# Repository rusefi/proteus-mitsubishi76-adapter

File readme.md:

https://github.com/rusefi/rusefi and https://github.com/mck1117/proteus

76 pin

2 gen DSM
1995-1999 Mitsubishi Eclipse and Eagle Talon Turbo DSM ECU Pinouts 

v6

Lancer up to 2005?

Our document, need work
[Connector Pinout Spreadsheet, with links to wiring drawings](https://docs.google.com/spreadsheets/d/1ZlcC5cdCwjYoV-z49MNaa9zpLiu_ZYBIx5H-j0F6QpI)

Norman notes https://docs.google.com/spreadsheets/d/1ddxDElQDG0ZjSaX5fpkFeflPWwk7OCHC93gru9Ey_9U

Random sources of info

https://my.prostreetonline.com/2013/09/05/faq-1g-and-2g-dsm-ecu-pinouts/

http://www.stealth316.com/2-ecu-terminals.htm

Compatible case:

MD329098

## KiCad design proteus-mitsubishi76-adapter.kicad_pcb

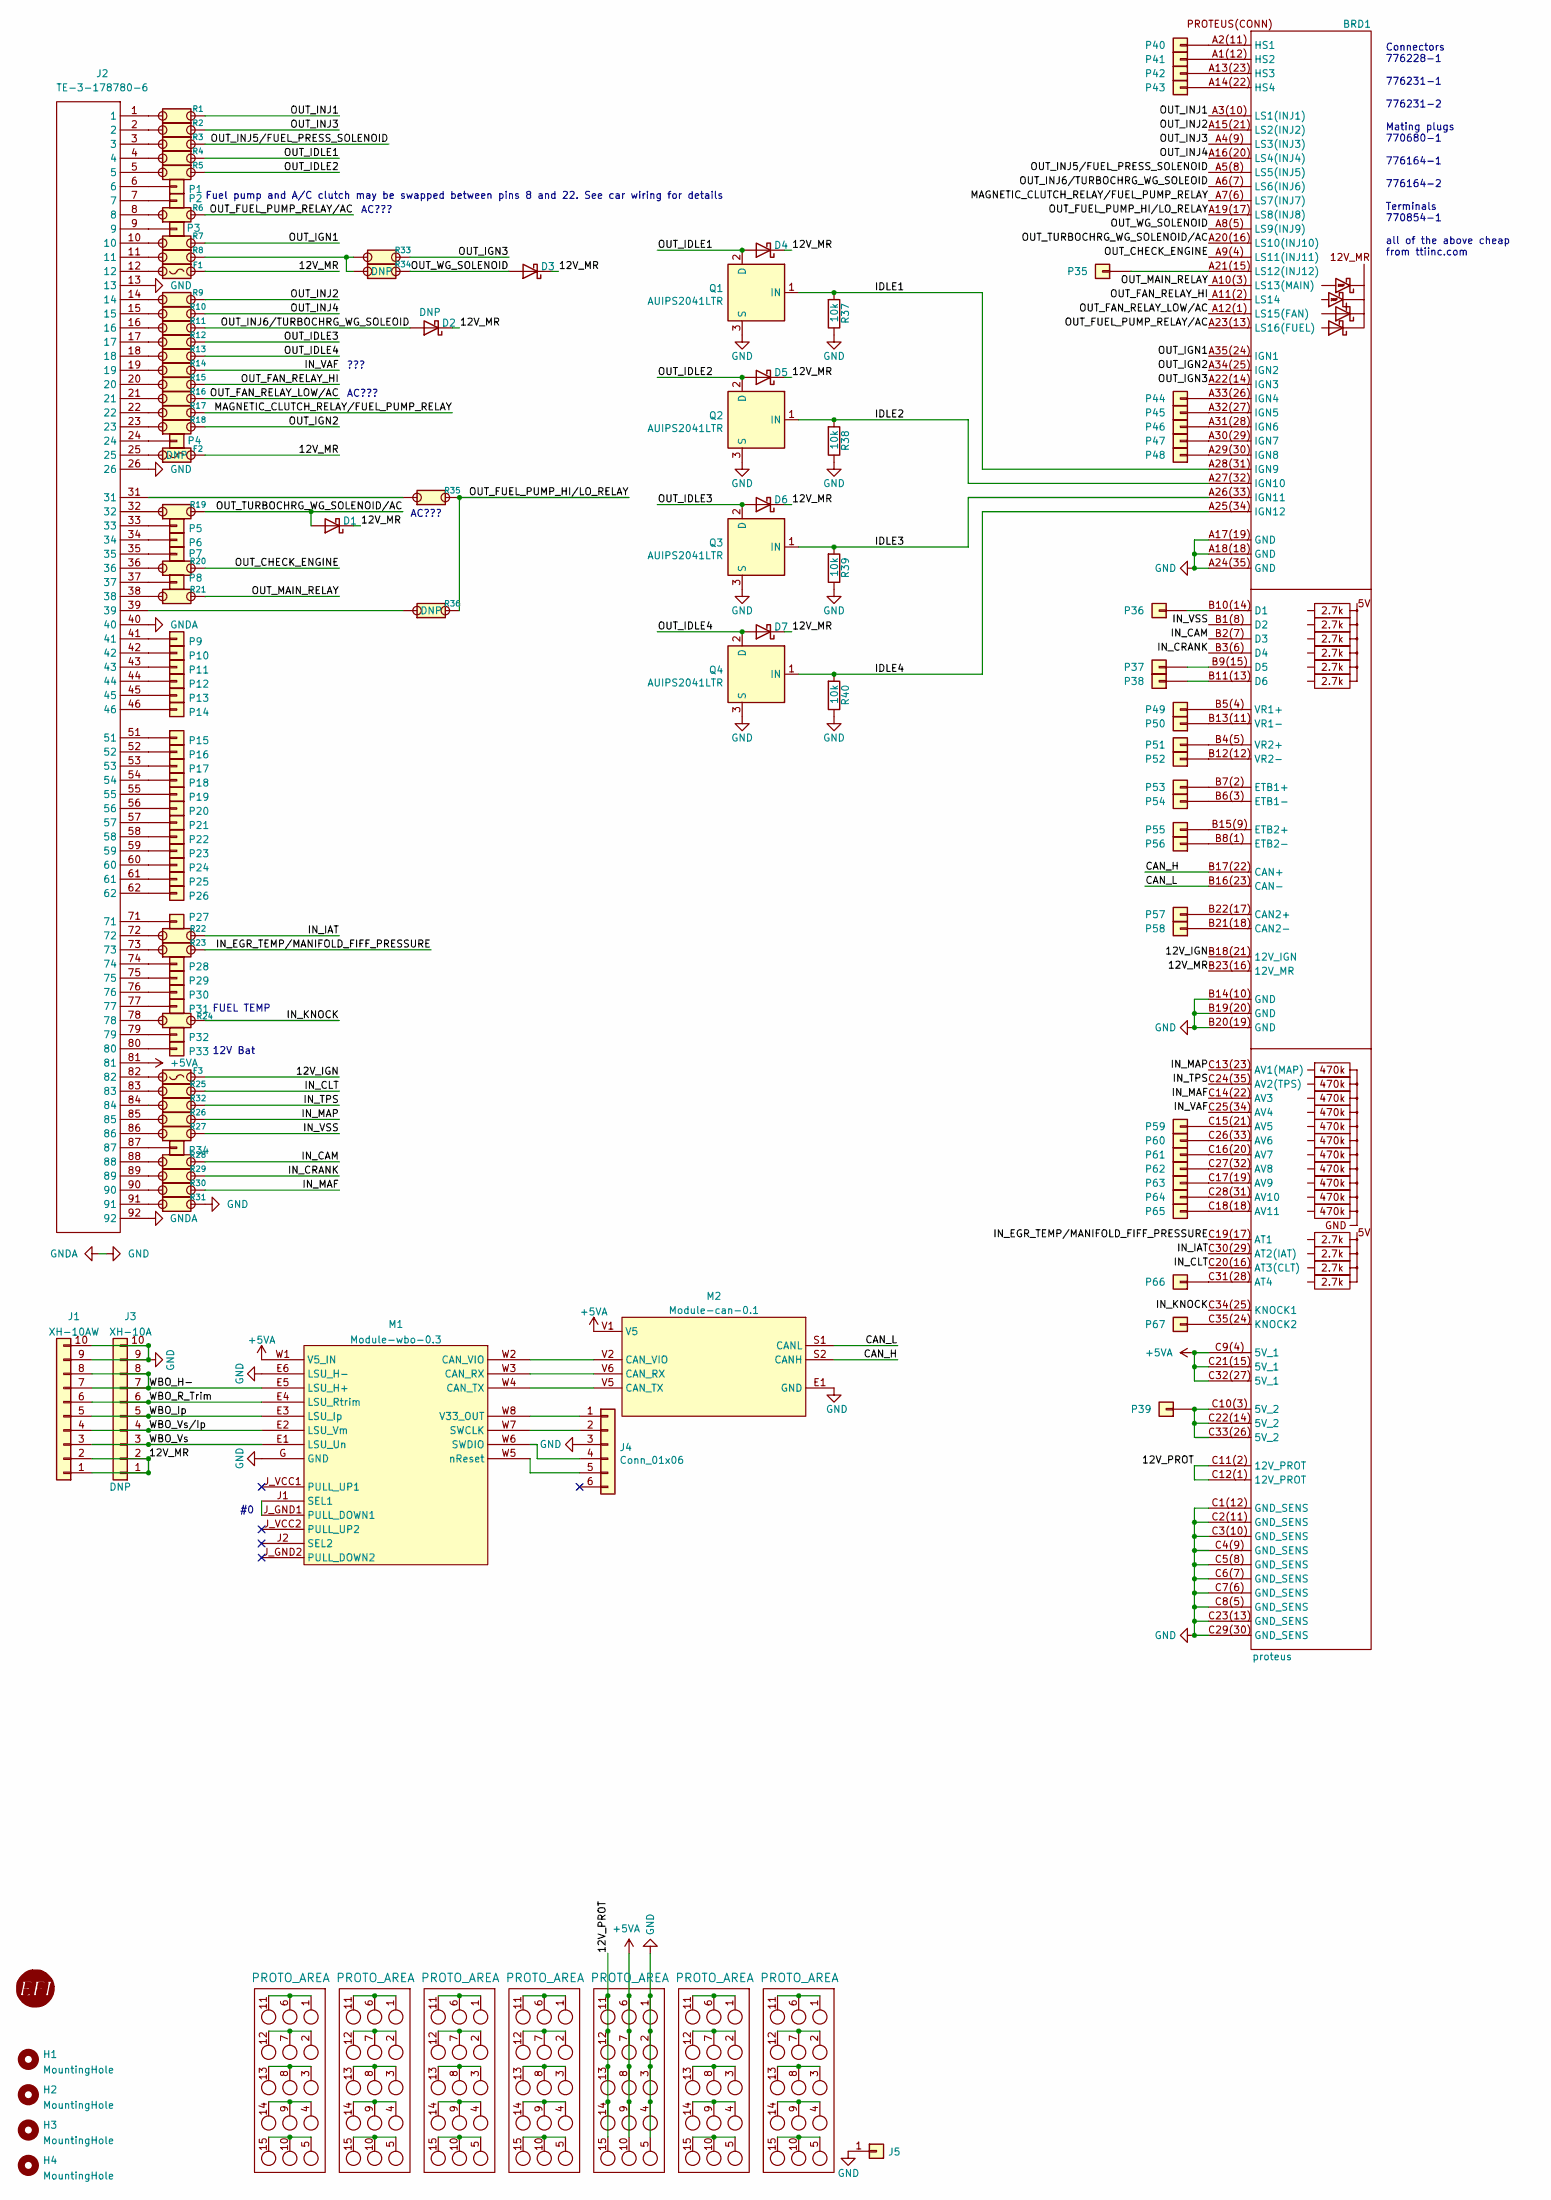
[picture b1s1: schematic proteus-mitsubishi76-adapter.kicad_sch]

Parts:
BRD1: proteus
D1, D3, D4, D5, D6, D7: D_Schottky; D_SMA; LCSC C8678
D2: DNP; D_SMA; LCSC_ext 0
F1, F3: Fuse-Pad-Pad; PAD-1206-PAD; LCSC C182446
F2: Fuse-Pad-Pad; PAD-1206-PAD
G1: RUSEFI_LOGO; rusefi_logo
G2, G3, G4, G5, G6, G7, G8: PROTO_AREA
H1, H2, H3, H4: MountingHole; MountingHole_5mm_Pad_TopOnly
J1: XH-10AW; JST_XH_S10B-XH-A_1x10_P2.50mm_Horizontal; LCSC C14652
J2: TE-3-178780-6
J3: XH-10A; JST_XH_B10B-XH-A_1x10_P2.50mm_Vertical; LCSC C8885
J4: Conn_01x06; PinHeader_1x06_P2.54mm_Vertical
J5: Conn_01x01; TestPoint_Pad_D4.0mm
M1: Module-wbo-0.3; wbo
M2: Module-can-0.1; can
P1, P2, P3, P4, P5, P6, P7, P8, P9, P10, P11, P12, P13, P14, P15, P16, P17, P18, P19, P20, P21, P22, P23, P24, P25, P26, P27, P28, P29, P30, P31, P32, P33, P34, P35, P36, P37, P38, P39, P40, P41, P42, P43, P44, P45, P46, P47, P48, P49, P50, P51, P52, P53, P54, P55, P56, P57, P58, P59, P60, P61, P62, P63, P64, P65, P66, P67: Pad; PAD-TH
Q1, Q2, Q3, Q4: AUIPS2041LTR; SOT-223; LCSC C113610
R1, R2, R3, R4, R5, R6, R7, R8, R9, R10, R11, R12, R13, R14, R15, R16, R17, R18, R19, R20, R21, R22, R23, R24, R25, R26, R27, R28, R29, R30, R31, R32, R33, R35: Jumper-Pad-Pad; PAD-0805-PAD; LCSC C17477
R34, R36: Jumper-Pad-Pad; PAD-0805-PAD
R37, R38, R39, R40: 10k; R_0402_1005Metric; LCSC C60489

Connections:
+5VA: BRD1.C9(4) (5V_1), BRD1.C21(15) (5V_1), BRD1.C32(27) (5V_1), G6.6, G6.7, G6.8, G6.9, G6.10, J2.81, M1.W1 (V5_IN), M2.V1 (V5)
/12V_IGN: BRD1.B18(21) (12V_IGN), F3.2
/12V_MR: BRD1.B23(16) (12V_MR), D1.1 (K), D2.1 (K), D3.1 (K), D4.1 (K), D5.1 (K), D6.1 (K), D7.1 (K), F1.2, F2.2, J1.1, J1.2, J3.1, J3.2
/12V_PROT: BRD1.C11(2) (12V_PROT), BRD1.C12(1) (12V_PROT), G6.11, G6.12, G6.13, G6.14, G6.15
/CAN_H: BRD1.B17(22) (CAN+), M2.S2 (CANH)
/CAN_L: BRD1.B16(23) (CAN-), M2.S1 (CANL)
/IDLE1: BRD1.A28(31) (IGN9), Q1.1 (IN), R37.2
/IDLE2: BRD1.A27(32) (IGN10), Q2.1 (IN), R38.2
/IDLE3: BRD1.A26(33) (IGN11), Q3.1 (IN), R39.2
/IDLE4: BRD1.A25(34) (IGN12), Q4.1 (IN), R40.2
/IN_CAM: BRD1.B2(7) (D3), R28.2
/IN_CLT: BRD1.C20(16) (AT3(CLT)), R25.2
/IN_CRANK: BRD1.B3(6) (D4), R29.2
/IN_EGR_TEMP/MANIFOLD_FIFF_PRESSURE: BRD1.C19(17) (AT1), R23.2
/IN_IAT: BRD1.C30(29) (AT2(IAT)), R22.2
/IN_KNOCK: BRD1.C34(25) (KNOCK1), R24.2
/IN_MAF: BRD1.C14(22) (AV3), R30.2
/IN_MAP: BRD1.C13(23) (AV1(MAP)), R26.2
/IN_TPS: BRD1.C24(35) (AV2(TPS)), R32.2
/IN_VAF: BRD1.C25(34) (AV4), R14.2
/IN_VSS: BRD1.B1(8) (D2), R27.2
/MAGNETIC_CLUTCH_RELAY/FUEL_PUMP_RELAY: BRD1.A7(6) (LS7(INJ7)), R17.2
/OUT_CHECK_ENGINE: BRD1.A9(4) (LS11(INJ11)), R20.2
/OUT_FAN_RELAY_HI: BRD1.A11(2) (LS14), R15.2
/OUT_FAN_RELAY_LOW/AC: BRD1.A12(1) (LS15(FAN)), R16.2
/OUT_FUEL_PUMP_HI/LO_RELAY: BRD1.A19(17) (LS8(INJ8)), R35.2, R36.2
/OUT_FUEL_PUMP_RELAY/AC: BRD1.A23(13) (LS16(FUEL)), R6.2
/OUT_IDLE1: D4.2 (A), Q1.2 (D), R4.2
/OUT_IDLE2: D5.2 (A), Q2.2 (D), R5.2
/OUT_IDLE3: D6.2 (A), Q3.2 (D), R12.2
/OUT_IDLE4: D7.2 (A), Q4.2 (D), R13.2
/OUT_IGN1: BRD1.A35(24) (IGN1), R7.2
/OUT_IGN2: BRD1.A34(25) (IGN2), R18.2
/OUT_IGN3: BRD1.A22(14) (IGN3), R33.2
/OUT_INJ1: BRD1.A3(10) (LS1(INJ1)), R1.2
/OUT_INJ2: BRD1.A15(21) (LS2(INJ2)), R9.2
/OUT_INJ3: BRD1.A4(9) (LS3(INJ3)), R2.2
/OUT_INJ4: BRD1.A16(20) (LS4(INJ4)), R10.2
/OUT_INJ5/FUEL_PRESS_SOLENOID: BRD1.A5(8) (LS5(INJ5)), R3.2
/OUT_INJ6/TURBOCHRG_WG_SOLEOID: BRD1.A6(7) (LS6(INJ6)), D2.2 (A), R11.2
/OUT_MAIN_RELAY: BRD1.A10(3) (LS13(MAIN)), R21.2
/OUT_TURBOCHRG_WG_SOLENOID/AC: BRD1.A20(16) (LS10(INJ10)), D1.2 (A), R19.2
/OUT_WG_SOLENOID: BRD1.A8(5) (LS9(INJ9)), D3.2 (A), R34.2
/WBO_H-: J1.7, J1.8, J3.7, J3.8, M1.E5 (LSU_H+)
/WBO_Ip: J1.5, J3.5, M1.E3 (LSU_Ip)
/WBO_R_Trim: J1.6, J3.6, M1.E4 (LSU_Rtrim)
/WBO_Vs: J1.3, J3.3, M1.E1 (LSU_Un)
/WBO_Vs/Ip: J1.4, J3.4, M1.E2 (LSU_Vm)
GND: BRD1.A17(19) (GND), BRD1.A18(18) (GND), BRD1.A24(35) (GND), BRD1.B14(10) (GND), BRD1.B19(20) (GND), BRD1.B20(19) (GND), BRD1.C1(12) (GND_SENS), BRD1.C2(11) (GND_SENS), BRD1.C3(10) (GND_SENS), BRD1.C4(9) (GND_SENS), BRD1.C5(8) (GND_SENS), BRD1.C6(7) (GND_SENS), BRD1.C7(6) (GND_SENS), BRD1.C8(5) (GND_SENS), BRD1.C23(13) (GND_SENS), BRD1.C29(30) (GND_SENS), G6.1, G6.2, G6.3, G6.4, G6.5, J1.9, J1.10, J2.13, J2.26, J2.40, J2.92, J3.9, J3.10, J4.3, J5.1, M1.E6 (LSU_H-), M1.G (GND), M2.E1 (GND), Q1.3 (S), Q2.3 (S), Q3.3 (S), Q4.3 (S), R31.2, R37.1, R38.1, R39.1, R40.1
unnamed: BRD1.A1(12) (HS2), P41.1
unnamed: BRD1.A2(11) (HS1), P40.1
unnamed: BRD1.A13(23) (HS3), P42.1
unnamed: BRD1.A14(22) (HS4), P43.1
unnamed: BRD1.A21(15) (LS12(INJ12)), P35.1
unnamed: BRD1.A29(30) (IGN8), P48.1
unnamed: BRD1.A30(29) (IGN7), P47.1
unnamed: BRD1.A31(28) (IGN6), P46.1
unnamed: BRD1.A32(27) (IGN5), P45.1
unnamed: BRD1.A33(26) (IGN4), P44.1
unnamed: BRD1.B4(5) (VR2+), P51.1
unnamed: BRD1.B5(4) (VR1+), P49.1
unnamed: BRD1.B6(3) (ETB1-), P54.1
unnamed: BRD1.B7(2) (ETB1+), P53.1
unnamed: BRD1.B8(1) (ETB2-), P56.1
unnamed: BRD1.B9(15) (D5), P37.1
unnamed: BRD1.B10(14) (D1), P36.1
unnamed: BRD1.B11(13) (D6), P38.1
unnamed: BRD1.B12(12) (VR2-), P52.1
unnamed: BRD1.B13(11) (VR1-), P50.1
unnamed: BRD1.B15(9) (ETB2+), P55.1
unnamed: BRD1.B21(18) (CAN2-), P58.1
unnamed: BRD1.B22(17) (CAN2+), P57.1
unnamed: BRD1.C10(3) (5V_2), BRD1.C22(14) (5V_2), BRD1.C33(26) (5V_2), P39.1
unnamed: BRD1.C15(21) (AV5), P59.1
unnamed: BRD1.C16(20) (AV7), P61.1
unnamed: BRD1.C17(19) (AV9), P63.1
unnamed: BRD1.C18(18) (AV11), P65.1
unnamed: BRD1.C26(33) (AV6), P60.1
unnamed: BRD1.C27(32) (AV8), P62.1
unnamed: BRD1.C28(31) (AV10), P64.1
unnamed: BRD1.C31(28) (AT4), P66.1
unnamed: BRD1.C35(24) (KNOCK2), P67.1
unnamed: F1.1, J2.12
unnamed: F2.1, J2.25
unnamed: F3.1, J2.82
unnamed: G2.1, G2.6, G2.11
unnamed: G2.5, G2.10, G2.15
unnamed: G2.2, G2.7, G2.12
unnamed: G2.3, G2.8, G2.13
unnamed: G2.4, G2.9, G2.14
unnamed: G3.1, G3.6, G3.11
unnamed: G3.5, G3.10, G3.15
unnamed: G3.2, G3.7, G3.12
unnamed: G3.3, G3.8, G3.13
unnamed: G3.4, G3.9, G3.14
unnamed: G4.1, G4.6, G4.11
unnamed: G4.5, G4.10, G4.15
unnamed: G4.2, G4.7, G4.12
unnamed: G4.3, G4.8, G4.13
unnamed: G4.4, G4.9, G4.14
unnamed: G5.1, G5.6, G5.11
unnamed: G5.5, G5.10, G5.15
unnamed: G5.2, G5.7, G5.12
unnamed: G5.3, G5.8, G5.13
unnamed: G5.4, G5.9, G5.14
unnamed: G7.1, G7.6, G7.11
unnamed: G7.5, G7.10, G7.15
unnamed: G7.2, G7.7, G7.12
unnamed: G7.3, G7.8, G7.13
unnamed: G7.4, G7.9, G7.14
unnamed: G8.1, G8.6, G8.11
unnamed: G8.5, G8.10, G8.15
unnamed: G8.2, G8.7, G8.12
unnamed: G8.3, G8.8, G8.13
unnamed: G8.4, G8.9, G8.14
unnamed: J2.1, R1.1
unnamed: J2.2, R2.1
unnamed: J2.3, R3.1
unnamed: J2.4, R4.1
unnamed: J2.5, R5.1
unnamed: J2.6, P1.1
unnamed: J2.7, P2.1
unnamed: J2.8, R6.1
unnamed: J2.9, P3.1
unnamed: J2.10, R7.1
unnamed: J2.11, R8.1
unnamed: J2.14, R9.1
unnamed: J2.15, R10.1
unnamed: J2.16, R11.1
unnamed: J2.17, R12.1
unnamed: J2.18, R13.1
unnamed: J2.19, R14.1
unnamed: J2.20, R15.1
unnamed: J2.21, R16.1
unnamed: J2.22, R17.1
unnamed: J2.23, R18.1
unnamed: J2.24, P4.1
unnamed: J2.31, R35.1
unnamed: J2.32, R19.1
unnamed: J2.33, P5.1
unnamed: J2.34, P6.1
unnamed: J2.35, P7.1
unnamed: J2.36, R20.1
unnamed: J2.37, P8.1
unnamed: J2.38, R21.1
unnamed: J2.39, R36.1
unnamed: J2.41, P9.1
unnamed: J2.42, P10.1
unnamed: J2.43, P11.1
unnamed: J2.44, P12.1
unnamed: J2.45, P13.1
unnamed: J2.46, P14.1
unnamed: J2.51, P15.1
unnamed: J2.52, P16.1
unnamed: J2.53, P17.1
unnamed: J2.54, P18.1
unnamed: J2.55, P19.1
unnamed: J2.56, P20.1
unnamed: J2.57, P21.1
unnamed: J2.58, P22.1
unnamed: J2.59, P23.1
unnamed: J2.60, P24.1
unnamed: J2.61, P25.1
unnamed: J2.62, P26.1
unnamed: J2.71, P27.1
unnamed: J2.72, R22.1
unnamed: J2.73, R23.1
unnamed: J2.74, P28.1
unnamed: J2.75, P29.1
unnamed: J2.76, P30.1
unnamed: J2.77, P31.1
unnamed: J2.78, R24.1
unnamed: J2.79, P32.1
unnamed: J2.80, P33.1
unnamed: J2.83, R25.1
unnamed: J2.84, R32.1
unnamed: J2.85, R26.1
unnamed: J2.86, R27.1
unnamed: J2.87, P34.1
unnamed: J2.88, R28.1
unnamed: J2.89, R29.1
unnamed: J2.90, R30.1
unnamed: J2.91, R31.1
unnamed: J4.1, M1.W8 (V33_OUT)
unnamed: J4.2, M1.W7 (SWCLK)
unnamed: J4.4, M1.W6 (SWDIO)
unnamed: J4.5, M1.W5 (nReset)
unnamed: M1.J1 (SEL1), M1.J_GND1 (PULL_DOWN1)
unnamed: M1.W2 (CAN_VIO), M2.V2 (CAN_VIO)
unnamed: M1.W3 (CAN_RX), M2.V6 (CAN_RX)
unnamed: M1.W4 (CAN_TX), M2.V5 (CAN_TX)
unnamed: R8.2, R33.1, R34.1

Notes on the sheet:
FUEL TEMP
AC???
???
Connectors 776228-1 776231-1 776231-2 Mating plugs 770680-1 776164-1 776164-2 Terminals 770854-1 all of the above cheap from ttiinc.com
Fuel pump and A/C clutch may be swapped between pins 8 and 22. See car wiring for details
12V Bat

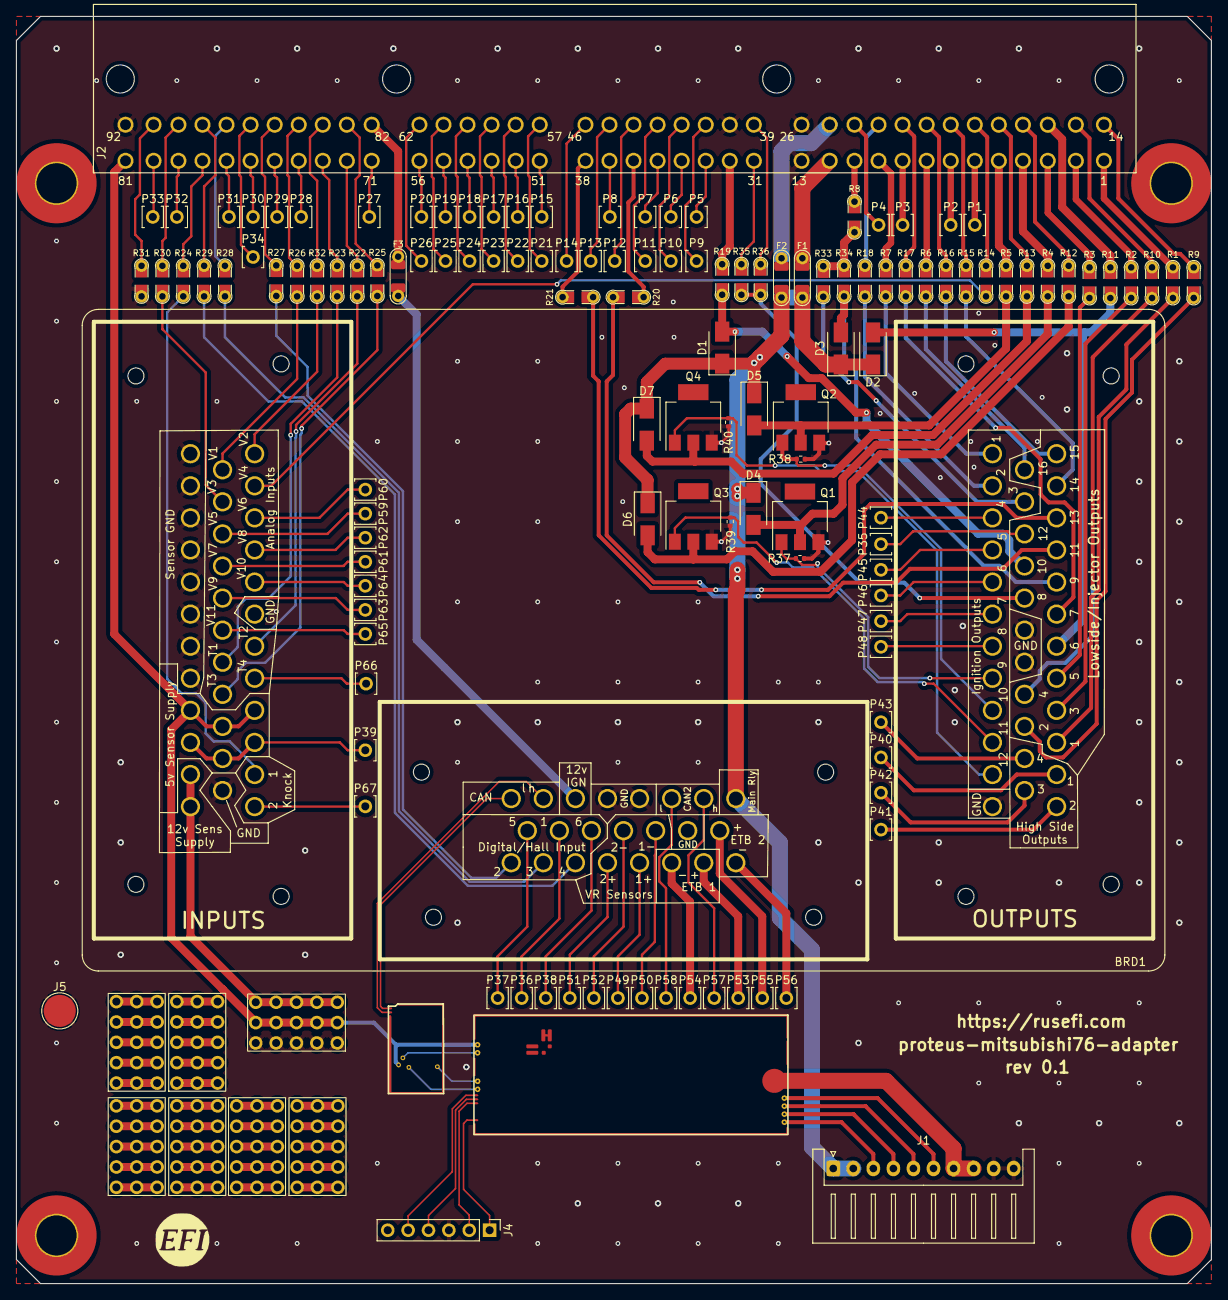
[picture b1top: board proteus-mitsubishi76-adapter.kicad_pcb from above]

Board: 2 copper layers, 149.0 x 158.0 mm, 140 parts (0 on the bottom side), 192 nets.

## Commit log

2021-10-25 76 pin footprint
2021-11-05 board outline
2021-12-06 Upd sch
2021-12-08 Starter pin, 8/22 pins note
2021-12-20 Board routing
2021-12-27 Add files via upload
    Pcb corrections.
2021-12-29 Fab preview
2021-12-29 fabbed!
2022-01-17 image
